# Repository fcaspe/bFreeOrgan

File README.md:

# bFreeOrgan
### A free Organ Synthesizer based on STM32F4.
**by Franco Caspe**

bFreeOrgan is an open source plattform for Additive Synthesis based on the well-regarded and low-cost Cortex M4 Microcontroller.
As of today, the plattform is used to implement a Synchronous Drawbar Organ Synthesizer that works with the STM32F407 Discovery board.
This project started in 2017, coded in C with ST Microelectronics Standard Peripheral Driver.

### Project state
This project is now IDE agnostic! Is built now with GNU make and arm gcc toolset.

[ARM GCC Toolset website](https://developer.arm.com/open-source/gnu-toolchain/gnu-rm/downloads)

For Flashing the discovery, the makefile uses texane/stlink tool. The latest version that is currently working fine for the STM32F4 Discovery board is 1.3.0.

[Texane's stlink utility](https://github.com/texane/stlink)

This repo currently contains the source and System Workbench project, KiCad project for the Main PCB and some calibration utils.
You can fancy your own drawbar controller (SEE PDF). 
3D Print Case is still pending! But, with a little creativity this project can be built! (see images)

### Building
Just make sure the arm-gcc toolset path is set in the PATH bash's enviroment variable when you run make.

1. Run: make
2. Connect the STM32F4 Discovery Board to the PC.
3. Run: make flash

### See it working!

[bFreeOrgan Prototype No.1](https://www.youtube.com/watch?v=Aql0KdO9ymM&t=1s)
### Some Images

Last Version PCB!

bFreeOrgan PCB with Discovery board mounted on.

Front Prototype Case

Rear Prototype Case

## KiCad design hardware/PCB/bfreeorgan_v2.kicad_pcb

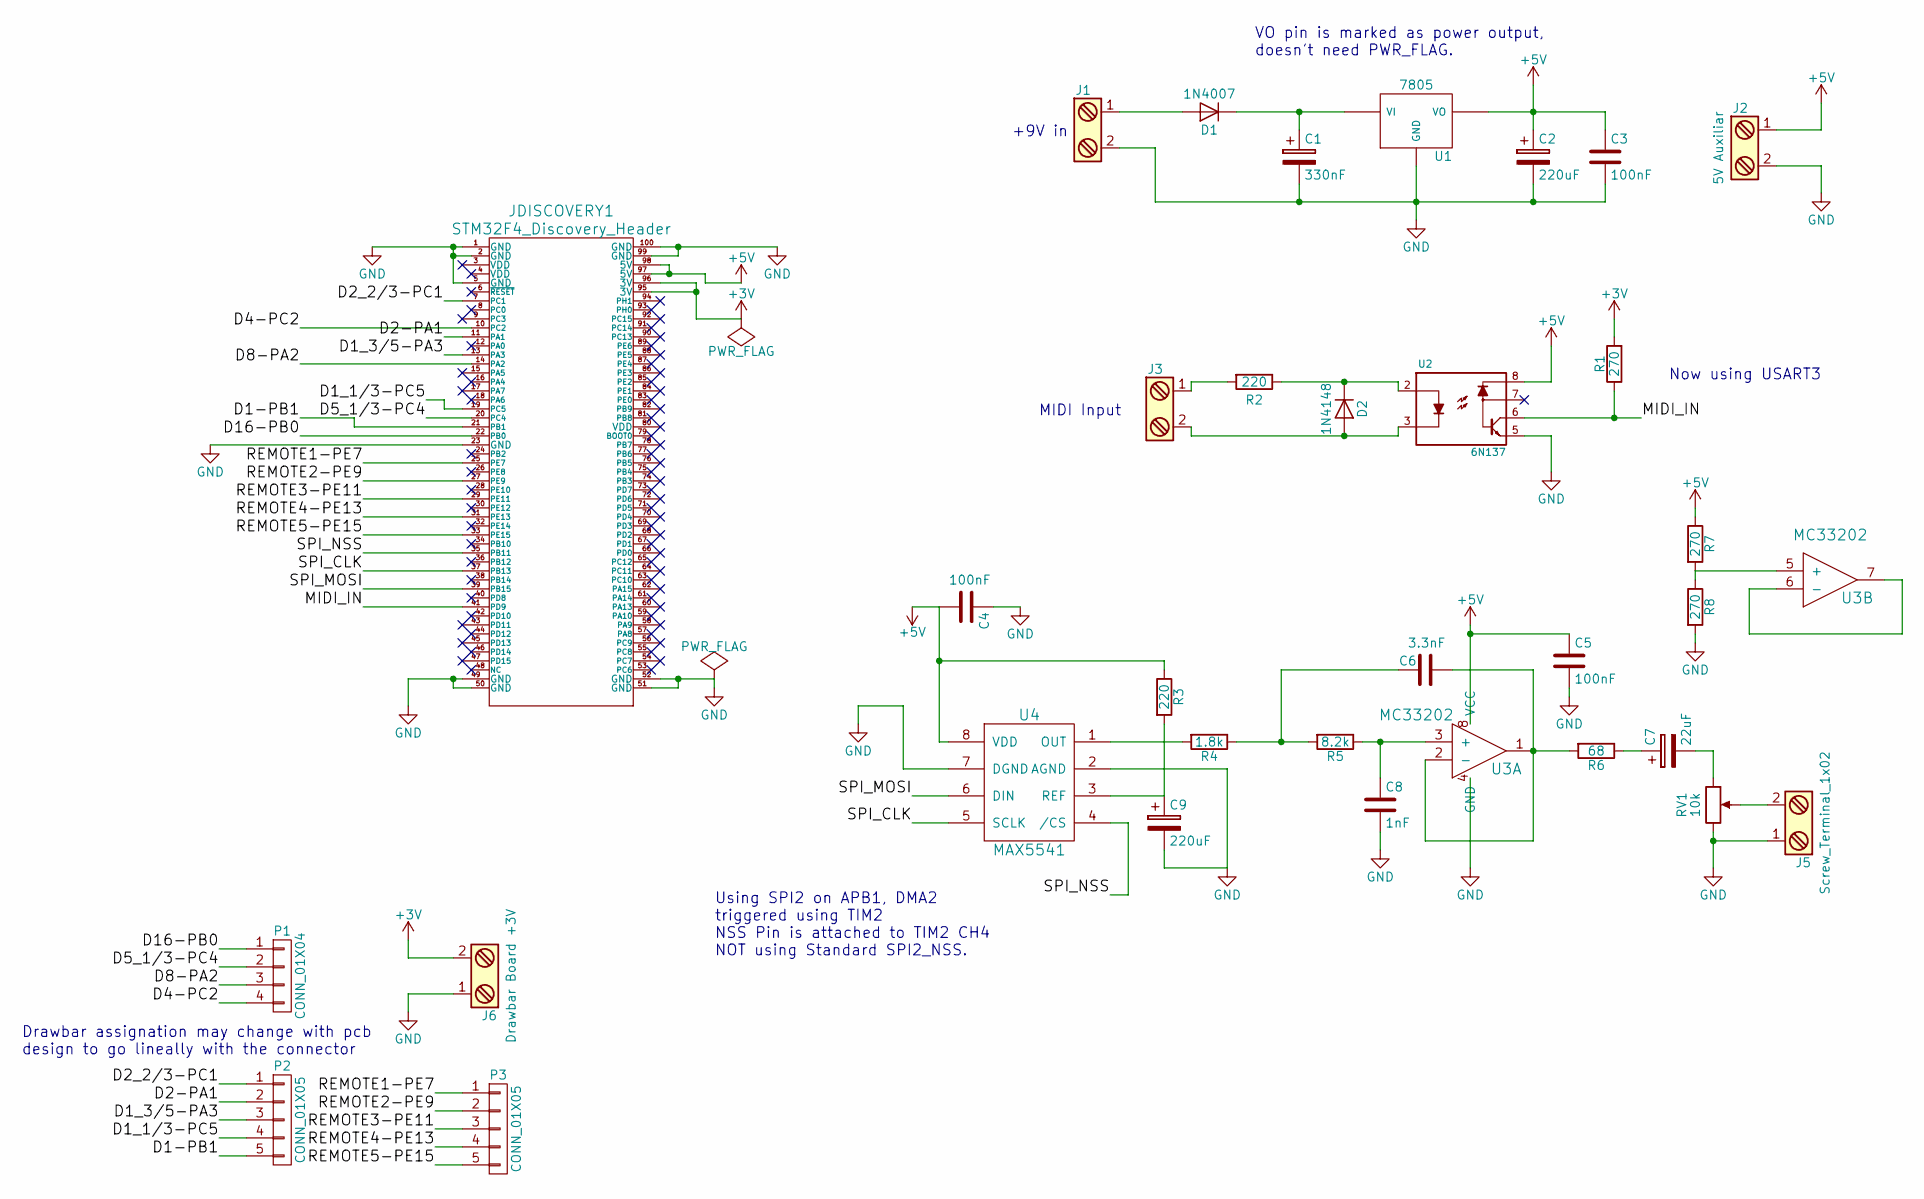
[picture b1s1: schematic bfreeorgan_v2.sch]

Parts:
C1: 330nF; C_Disc_D3_P2.5
C2, C9: 220uF; C_Radial_D8_L21_P3.8
C3, C4, C5: 100nF; C_Disc_D3_P2.5
C6: 3.3nF; C_Disc_D3_P2.5
C7: 22uF; C_Radial_D5_L11_P2.5
C8: 1nF; C_Disc_D3_P2.5
D1: 1N4007; Diode_DO-41_SOD81_Horizontal_RM10
D2: 1N4148; Diode_DO-35_SOD27_Horizontal_RM10
J1, J3, J5: Screw_Terminal_1x02; bornier2
J2: 5V Auxiliar; bornier2
J6: Drawbar Board +3V; bornier2
JDISCOVERY1: STM32F4_Discovery_Header; stm32f4_discovery_header
P1: CONN_01X04; Pin_Header_Straight_1x04
P2, P3: CONN_01X05; Pin_Header_Straight_1x05
R1, R7, R8: 270; Resistor_Horizontal_RM10mm
R2, R3: 220; Resistor_Horizontal_RM10mm
R4: 1.8k; Resistor_Horizontal_RM10mm
R5: 8.2k; Resistor_Horizontal_RM10mm
R6: 68; Resistor_Horizontal_RM10mm
RV1: 10k; bornier3
U1: 7805; TO-220_Neutral123_Vertical
U2: 6N137; DIP-8_W7.62mm
U3: MC33202; SOIC-8-N
U4: MAX5541; SOIC-8-N

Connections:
+3V: J6.2, JDISCOVERY1.95 (3V), JDISCOVERY1.96 (3V), R1.2; also elsewhere on the board
+5V: C2.1, C3.1, C4.2, C5.1, J2.1, JDISCOVERY1.97 (5V), JDISCOVERY1.98 (5V), R3.1, R7.1, U1.3 (VO), U2.8, U3.8 (VCC), U4.8 (VDD); also elsewhere on the board
/D1-PB1: JDISCOVERY1.21 (PB1), P2.5; also elsewhere on the board
/D1_1/3-PA3: JDISCOVERY1.13 (PA3), P2.3; also elsewhere on the board
/D1_3/5-PA1: JDISCOVERY1.11 (PA1), P2.2; also elsewhere on the board
/D2_2/3-PC1: JDISCOVERY1.7 (PC1), P2.1; also elsewhere on the board
/D4-PC2: JDISCOVERY1.10 (PC2), P1.4; also elsewhere on the board
/D5_1/3-PA2: JDISCOVERY1.14 (PA2), P1.3; also elsewhere on the board
/D16-PB0: JDISCOVERY1.22 (PB0), P1.1; also elsewhere on the board
/DX-PC4: JDISCOVERY1.20 (PC4), P1.2; also elsewhere on the board
/DX-PC5: JDISCOVERY1.19 (PC5), P2.4; also elsewhere on the board
/MIDI_IN: JDISCOVERY1.41 (PD9), R1.1, U2.6; also elsewhere on the board
/REMOTE1: JDISCOVERY1.25 (PE7), P3.1; also elsewhere on the board
/REMOTE2: JDISCOVERY1.27 (PE9), P3.2; also elsewhere on the board
/REMOTE3: JDISCOVERY1.29 (PE11), P3.3; also elsewhere on the board
/REMOTE4: JDISCOVERY1.31 (PE13), P3.4; also elsewhere on the board
/REMOTE5: JDISCOVERY1.33 (PE15), P3.5; also elsewhere on the board
/SPI_CLK: JDISCOVERY1.37 (PB13), U4.5 (SCLK); also elsewhere on the board
/SPI_MOSI: JDISCOVERY1.39 (PB15), U4.6 (DIN); also elsewhere on the board
/SPI_NSS: JDISCOVERY1.35 (PB11), U4.4 (/CS); also elsewhere on the board
GND: C1.2, C2.2, C3.2, C4.1, C5.2, C8.2, C9.2, J1.2, J2.2, J5.1, J6.1, JDISCOVERY1.1 (GND), JDISCOVERY1.2 (GND), JDISCOVERY1.5 (GND), JDISCOVERY1.23 (GND), JDISCOVERY1.49 (GND), JDISCOVERY1.50 (GND), JDISCOVERY1.51 (GND), JDISCOVERY1.52 (GND), JDISCOVERY1.99 (GND), JDISCOVERY1.100 (GND), R8.2, RV1.3, U1.2 (GND), U2.5, U3.4 (GND), U4.2 (AGND), U4.7 (DGND); also elsewhere on the board
unnamed: C1.1, D1.1 (K), U1.1 (VI)
unnamed: C6.1, R6.2, U3.1, U3.2 (-)
unnamed: C6.2, R4.1, R5.2
unnamed: C7.1, R6.1
unnamed: C7.2, RV1.1
unnamed: C8.1, R5.1, U3.3 (+)
unnamed: C9.1, R3.2, U4.3 (REF)
unnamed: D1.2 (A), J1.1
unnamed: D2.1 (K), R2.1, U2.2
unnamed: D2.2 (A), J3.2, U2.3
unnamed: J3.1, R2.2
unnamed: J5.2, RV1.2
unnamed: R4.2, U4.1 (OUT)
unnamed: R7.2, R8.1, U3.5 (+)
unnamed: U3.6 (-), U3.7

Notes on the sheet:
+9V in
Using SPI2 on APB1, DMA2 triggered using TIM2 NSS Pin is attached to TIM2 CH4 NOT using Standard SPI2_NSS.
Now using USART3
MIDI Input
VO pin is marked as power output, doesn't need PWR_FLAG.
Drawbar assignation may change with pcb design to go lineally with the connector

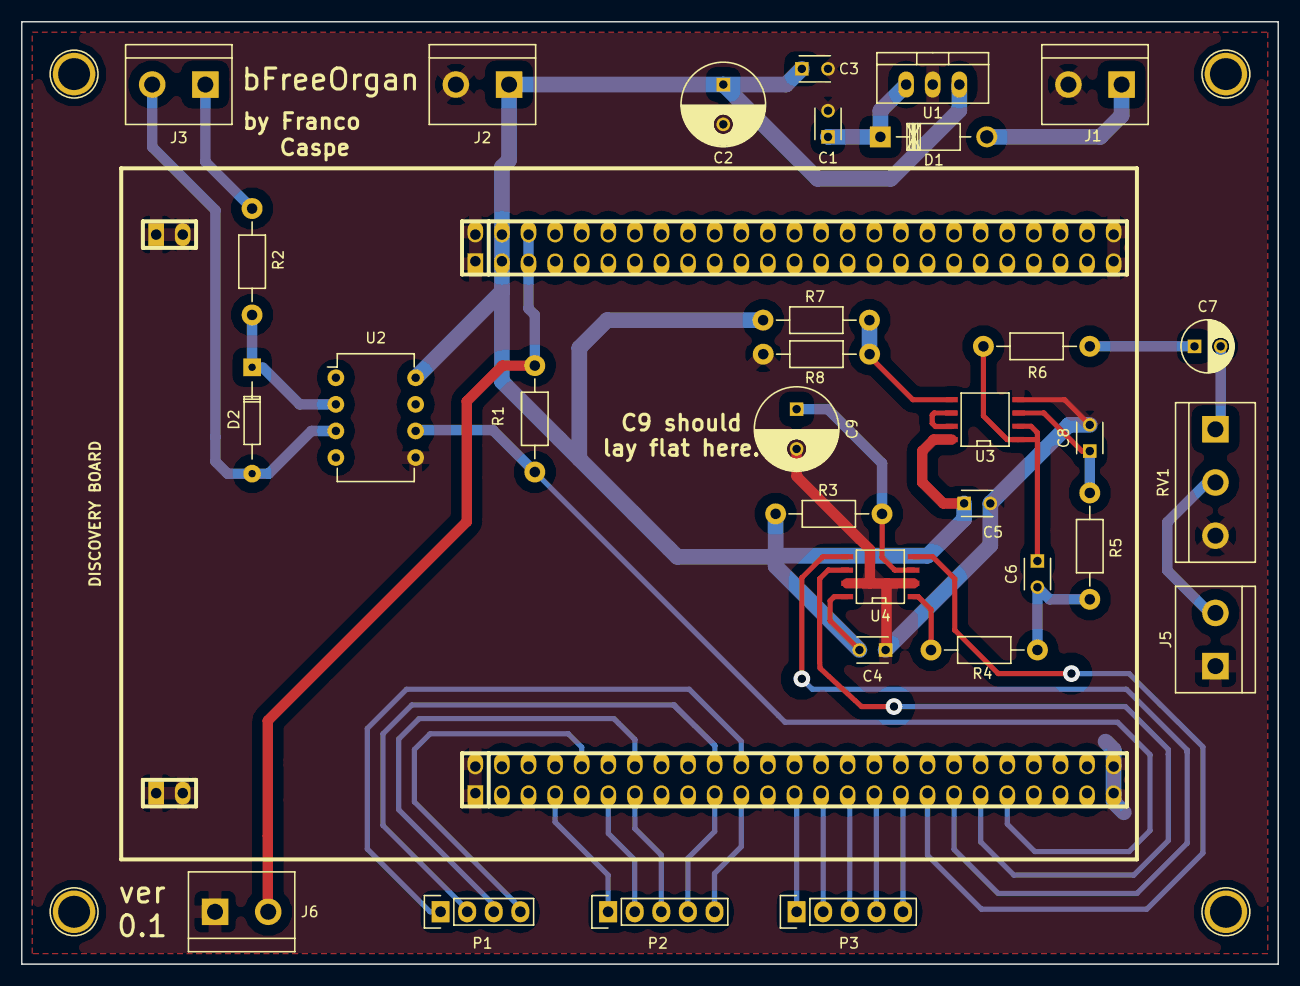
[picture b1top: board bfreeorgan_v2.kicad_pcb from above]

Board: 2 copper layers, 120.0 x 90.0 mm, 33 parts (0 on the bottom side), 36 nets.

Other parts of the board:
DISCOVERY BOARD: STM32F4_Discovery_Header; stm32f4_discovery_header

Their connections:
+3V: DISCOVERY BOARD.95, DISCOVERY BOARD.96; also elsewhere on the board
+5V: DISCOVERY BOARD.97, DISCOVERY BOARD.98; also elsewhere on the board
/D1-PB1: DISCOVERY BOARD.21; also elsewhere on the board
/D1_1/3-PA3: DISCOVERY BOARD.13; also elsewhere on the board
/D1_3/5-PA1: DISCOVERY BOARD.11; also elsewhere on the board
/D2_2/3-PC1: DISCOVERY BOARD.7; also elsewhere on the board
/D4-PC2: DISCOVERY BOARD.10; also elsewhere on the board
/D5_1/3-PA2: DISCOVERY BOARD.14; also elsewhere on the board
/D16-PB0: DISCOVERY BOARD.22; also elsewhere on the board
/DX-PC4: DISCOVERY BOARD.20; also elsewhere on the board
/DX-PC5: DISCOVERY BOARD.19; also elsewhere on the board
/MIDI_IN: DISCOVERY BOARD.41; also elsewhere on the board
/REMOTE1: DISCOVERY BOARD.25; also elsewhere on the board
/REMOTE2: DISCOVERY BOARD.27; also elsewhere on the board
/REMOTE3: DISCOVERY BOARD.29; also elsewhere on the board
/REMOTE4: DISCOVERY BOARD.31; also elsewhere on the board
/REMOTE5: DISCOVERY BOARD.33; also elsewhere on the board
/SPI_CLK: DISCOVERY BOARD.37; also elsewhere on the board
/SPI_MOSI: DISCOVERY BOARD.39; also elsewhere on the board
/SPI_NSS: DISCOVERY BOARD.35; also elsewhere on the board
GND: DISCOVERY BOARD.1, DISCOVERY BOARD.2, DISCOVERY BOARD.5, DISCOVERY BOARD.23, DISCOVERY BOARD.49, DISCOVERY BOARD.50, DISCOVERY BOARD.51, DISCOVERY BOARD.52, DISCOVERY BOARD.99, DISCOVERY BOARD.100; also elsewhere on the board

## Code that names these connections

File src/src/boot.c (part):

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   * |---|----------|-------|---------------|
   * |POS|DRAWBAR	|GPIO	|ADC CHANNEL	|
   * |---|----------|-------|---------------|
   * |0	 |16		|PB0	|8				|
   * |1	 |5 1/3		|PC4	|14				|
   * |2	 |8			|PA2	|2				|
   * |3	 |4			|PC2	|12				|
   * |4	 |2 2/3		|PC1	|11				|
   * |5	 |2			|PA1	|1				|
   * |6	 |1 3/5		|PA3	|3				|
   * |7	 |1 1/3		|PC5	|15				|
   * |8	 |1			|PB1	|9				|
   * |---|----------|-------|---------------|
   */

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	SPI_Cmd(SPI2, ENABLE);
	/*	GPIO CONFIGURATION	*/

	/* PB11 Timer OC Output. - TIM2 CH4 (NSS) */
	/* PB13 SPI CLK Output. (SPI2_SCK) */
	/* PB15 SPI MOSI (SPI2_MOSI) */

	GPIO_PinAFConfig(GPIOB,GPIO_PinSource11,GPIO_AF_TIM2);
	GPIO_PinAFConfig(GPIOB,GPIO_PinSource13,GPIO_AF_SPI2);
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
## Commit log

2018-01-29 Added Source and Project files.
2018-01-29 Added TODO.txt file
2018-10-09 New v2: Added KiCad PCB supporting external DAC. Updated firmware. Added calibration utils.
2018-10-09 New version cleaning.
2018-10-09 Added README and TODO
2018-10-10 Fixed README.md
2018-12-03 Add LICENSE.txt
2018-12-14 Added Video Link.
2018-12-14 Add Link
2019-02-20 Moved project to GNU Make. Added Drawbar controller schematic.
2019-02-20 Modified README.md
